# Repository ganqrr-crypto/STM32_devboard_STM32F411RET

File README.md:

I am making this project to learn better the STM cause i really like the programming of it and because i heard it's precise and i think that's nice. I am making this so i can make it 4 layers too and i feel like i've learned alot doing this. I think i will like this microcontroller and im gonna use it in different projects. BUT it's very pricy.

# Features

This project uses a STM32F411RET6 as MCU and it features USB C and a power led but no built in gpio led.
I made it a 4 layer board because i would have cleaner routing and interrupted ground plane under usb d+ and d- and so easier routing for the gpio pins.
It uses a 12MHz crystal that is close to the chip and has the RESET and BOOT buttons.

The PCB is green so the PCB wouldn't end up too expensive because JLCPCB charges money on 4 layer colored PCB.

This devboard uses 603 capacitors,leds and resistors so it can be more compact and has 4 holes for possible mounting.

# NRST Button notes

*The RESET button is NRST.

# Important folder locations

The gerbers are found in the "Manufacturing" folder and the 3D STEP model of the PCB is found in the "CAD" folder.

# PCB

I designed this PCB in Ki Cad

This is the PCB 3d render

And on the back it has also GPIO silkscreen so when connecting pins is easier

Here is the schematic picture:

And here are the PCB routing pictures
LAYER 1 :

LAYER2:

LAYER3:

LAYER4:

No ground plane picture:

# BOM

BOM: 
| Part | Quantity | Cost USD | Vendor | Link |
|------|----------|----------|--------|------|
| STM32F411RET6 | 1 | $10.74 | TME | [link](https://www.tme.eu/it/details/stm32f411ret6/microcontrollori-st/stmicroelectronics/) |
| 100nF capacitor | 15 | $0.59 | TME | [link](https://www.tme.eu/it/details/0603b104k500ct/condensatori-mlcc-smd/walsin/) |
| 1uF capacitor | 10 | $0.46 | TME | [link](https://www.tme.eu/it/details/0603b105k160ct/condensatori-mlcc-smd/walsin/) |
| 22pF capacitor | 10 | $0.2 | TME | [link](https://www.tme.eu/it/details/0603n220j500ct/condensatori-mlcc-smd/walsin/) |
| 10uF capacitor | 5 | $1.49 | TME | [link](https://www.tme.eu/it/details/c0603c106m9pac/condensatori-mlcc-smd/kemet/c0603c106m9pactu/) |
| 4.7uF capacitor | 2 | $0.91 | TME | [link](https://www.tme.eu/it/details/c0603c475k8pac/condensatori-mlcc-smd/kemet/c0603c475k8pactu/) |
| LED 603 | 2 | $1.32 | TME | [link](https://www.tme.eu/it/details/sm0603gcl/diodi-led-smd-colorati/bivar/) |
| USB 4105 | 1 | $0.88 | TME | [link](https://www.tme.eu/it/details/usb4105-gf-a/connettori-usb-e-ieee-1394/gct/) |
| 5k1 Resistor | 10 | $0.19 | TME | [link](https://www.tme.eu/it/details/ac0603fr-075k1l/resistori-smd/yageo/) |
| 10K Resistor | 10 | $0.25 | TME | [link](https://www.tme.eu/it/details/rc0603fr-0710k/resistori-smd/yageo/rc0603fr-0710kl/) |
| 1k Resistor | 10 | $0.18 | TME | [link](https://www.tme.eu/it/details/rc0603fr-071k/resistori-smd/yageo/rc0603fr-071kl/) |
| Buttons | 2 | $2.18 | TME | [link](https://www.tme.eu/it/details/b3u-1000p/microinterruttori-tact/aratas-formerly-omron-components/) |
| USBLC6-2SC6 | 1 | $0.55 | TME | [link](https://www.tme.eu/it/details/usblc6-2sc6/diodi-di-protezione-reti/stmicroelectronics/) |
| TLV75733PDBVR | 2 | $0.6 | TME | [link](https://www.tme.eu/it/details/tlv75733pdbvr/stabilizzatori-di-tens-non-regol-ldo/texas-instruments/) |
| 12MHz crystal | 1 | $0.61 | TME | [link](https://www.tme.eu/it/en/details/abm3b-12.000mhz-b2/resonators-and-generators/abracon/abm3b-12-000mhz-b2-t/) |
| Headers | 10 | $2.02 | TME | [link](https://www.tme.eu/it/en/details/zl201-16g/pin-headers/connfly/ds1021-1-16sf11/) |
| PCB | 5 | $9.83 | JLCPCB | |
| **TOTAL WITH TAX AND SHIPPING** | | **$41.20** | | |

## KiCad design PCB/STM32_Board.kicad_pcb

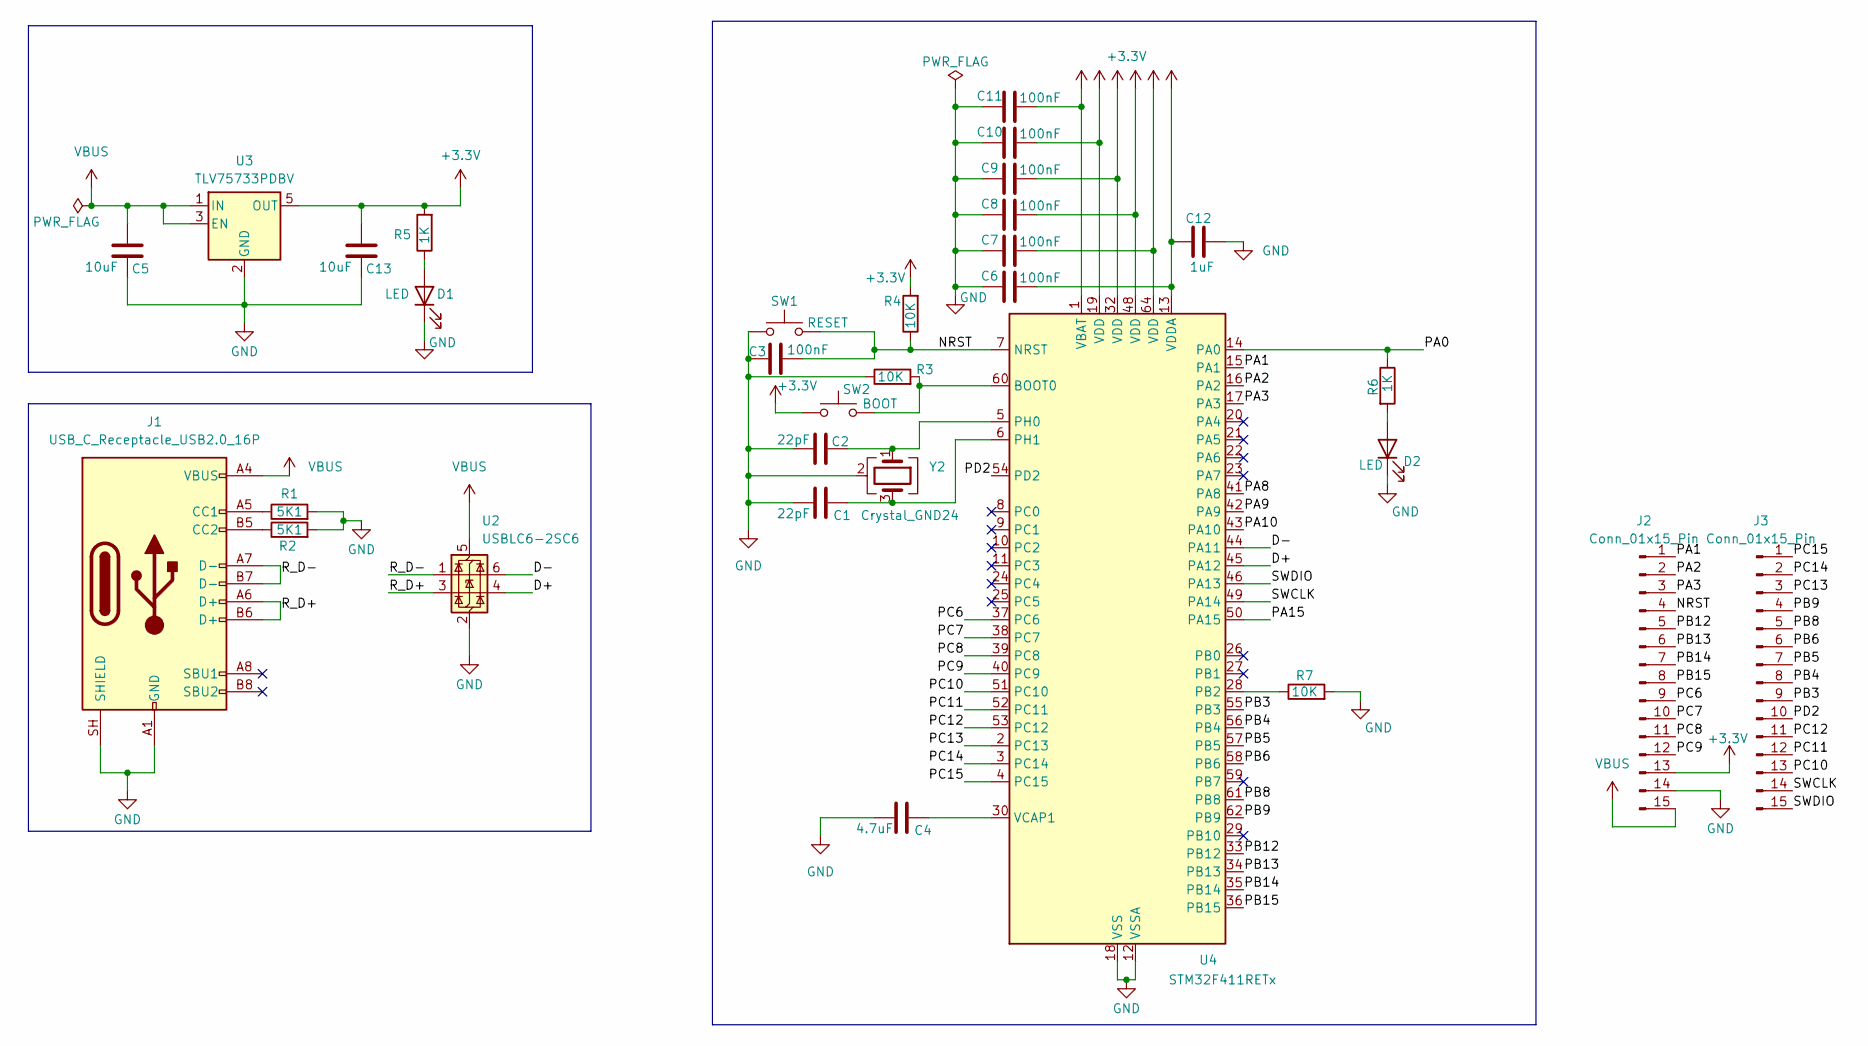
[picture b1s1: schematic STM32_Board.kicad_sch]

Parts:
C1, C2: 22pF; C_0603_1608Metric_Pad1.08x0.95mm_HandSolder
C3, C6, C7, C8, C9, C10, C11: 100nF; C_0603_1608Metric_Pad1.08x0.95mm_HandSolder
C4: 4.7uF; C_0603_1608Metric_Pad1.08x0.95mm_HandSolder
C5, C13: 10uF; C_0603_1608Metric_Pad1.08x0.95mm_HandSolder
C12: 1uF; C_0603_1608Metric_Pad1.08x0.95mm_HandSolder
D1, D2: LED; LED_0603_1608Metric_Pad1.05x0.95mm_HandSolder
J1: USB_C_Receptacle_USB2.0_16P; USB_C_Receptacle_GCT_USB4105-xx-A_16P_TopMnt_Horizontal
J2, J3: Conn_01x15_Pin; PinHeader_1x15_P2.54mm_Vertical
R1, R2: 5K1; R_0603_1608Metric_Pad0.98x0.95mm_HandSolder
R3, R4, R7: 10K; R_0603_1608Metric_Pad0.98x0.95mm_HandSolder
R5, R6: 1K; R_0603_1608Metric_Pad0.98x0.95mm_HandSolder
SW1: RESET; SW_SPST_B3U-1000P
SW2: BOOT; SW_SPST_B3U-1000P
U2: USBLC6-2SC6; SOT-23-6
U3: TLV75733PDBV; SOT-23-5
U4: STM32F411RETx; LQFP-64_10x10mm_P0.5mm
Y2: Crystal_GND24; Crystal_SMD_Abracon_ABM3B-4Pin_5.0x3.2mm

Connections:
+3.3V: C6.2, C7.2, C8.2, C9.2, C10.2, C11.2, C12.2, C13.1, J2.13, R4.2, R5.2, SW2.1, U3.5 (OUT), U4.1 (VBAT), U4.13 (VDDA), U4.19 (VDD), U4.32 (VDD), U4.48 (VDD), U4.64 (VDD); also elsewhere on the board
/D+: U2.4 (I/O2), U4.45 (PA12)
/D-: U2.6 (I/O1), U4.44 (PA11)
/NRST: C3.2, J2.4, R4.1, SW1.2, U4.7 (NRST); also elsewhere on the board
/PA0: R6.1, U4.14 (PA0)
/PA1: J2.1, U4.15 (PA1)
/PA2: J2.2, U4.16 (PA2)
/PA3: J2.3, U4.17 (PA3)
/PA8: U4.41 (PA8)
/PA9: U4.42 (PA9)
/PA10: U4.43 (PA10)
/PA15: U4.50 (PA15)
/PB3: J3.9, U4.55 (PB3)
/PB4: J3.8, U4.56 (PB4)
/PB5: J3.7, U4.57 (PB5)
/PB6: J3.6, U4.58 (PB6)
/PB8: J3.5, U4.61 (PB8)
/PB9: J3.4, U4.62 (PB9)
/PB12: J2.5, U4.33 (PB12)
/PB13: J2.6, U4.34 (PB13)
/PB14: J2.7, U4.35 (PB14)
/PB15: J2.8, U4.36 (PB15)
/PC6: J2.9, U4.37 (PC6)
/PC7: J2.10, U4.38 (PC7)
/PC8: J2.11, U4.39 (PC8)
/PC9: J2.12, U4.40 (PC9)
/PC10: J3.13, U4.51 (PC10)
/PC11: J3.12, U4.52 (PC11)
/PC12: J3.11, U4.53 (PC12)
/PC13: J3.3, U4.2 (PC13)
/PC14: J3.2, U4.3 (PC14)
/PC15: J3.1, U4.4 (PC15)
/PD2: J3.10, U4.54 (PD2)
/R_D+: J1.A6 (D+), J1.B6 (D+), U2.3 (I/O2)
/R_D-: J1.A7 (D-), J1.B7 (D-), U2.1 (I/O1)
/SWCLK: J3.14, U4.49 (PA14)
/SWDIO: J3.15, U4.46 (PA13)
GND: C1.1, C2.1, C3.1, C4.1, C5.2, C6.1, C7.1, C8.1, C9.1, C10.1, C11.1, C12.1, C13.2, D1.1 (K), D2.1 (K), J1.A1 (GND), J1.A12 (GND), J1.B1 (GND), J1.B12 (GND), J1.SH (SHIELD), J2.14, R1.2, R2.2, R3.1, R7.2, SW1.1, U2.2 (GND), U3.2 (GND), U4.12 (VSSA), U4.18 (VSS), U4.31 (VSS), U4.47 (VSS), U4.63 (VSS), Y2.2 (G), Y2.4 (G); also elsewhere on the board
unnamed: D1.2 (A), R5.1
unnamed: D2.2 (A), R6.2
unnamed: J1.A5 (CC1), R1.1
unnamed: J1.B5 (CC2), R2.1
unnamed 42: R3.2, SW2.2, U4.60 (BOOT0); also elsewhere on the board
unnamed: R7.1, U4.28 (PB2)
unnamed: C2.2, U4.5 (PH0), Y2.1
unnamed: C1.2, U4.6 (PH1), Y2.3
unnamed: C4.2, U4.30 (VCAP1)
VBUS: C5.1, J1.A4 (VBUS), J1.A9 (VBUS), J1.B4 (VBUS), J1.B9 (VBUS), J2.15, U2.5 (VBUS), U3.1 (IN), U3.3 (EN)

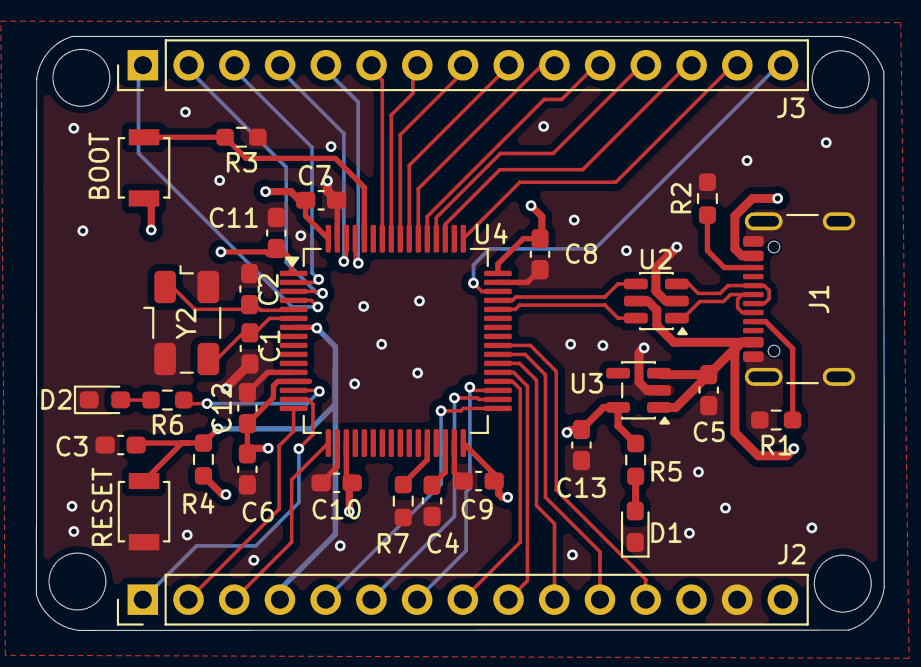
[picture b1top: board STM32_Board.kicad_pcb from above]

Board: 4 copper layers, 47.1 x 33.0 mm, 31 parts (0 on the bottom side), 44 nets.

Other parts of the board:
BOOT: BOOT; SW_SPST_B3U-1000P
RESET: RESET; SW_SPST_B3U-1000P

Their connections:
+3.3V: BOOT.1; also elsewhere on the board
/NRST: RESET.2; also elsewhere on the board
GND: RESET.1; also elsewhere on the board
unnamed 42: BOOT.2; also elsewhere on the board
